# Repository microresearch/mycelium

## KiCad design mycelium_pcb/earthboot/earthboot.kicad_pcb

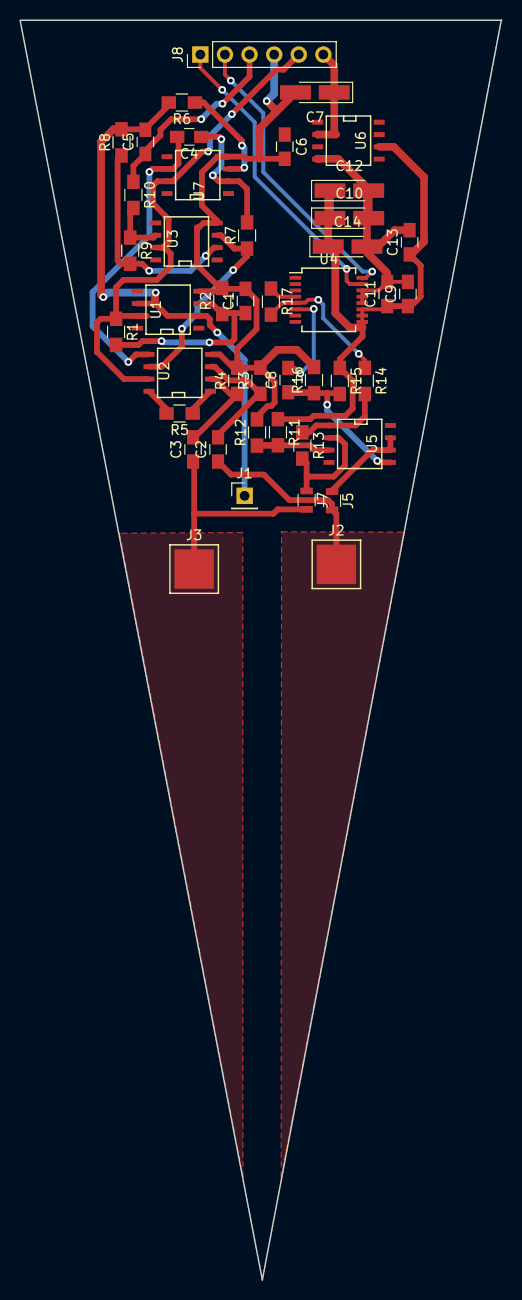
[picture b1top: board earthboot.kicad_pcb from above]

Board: 2 copper layers, 49.7 x 130.0 mm, 44 parts (0 on the bottom side), 29 nets.

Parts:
C1, C4: 100N; C_0805_HandSoldering
C2, C3: 10n; C_0805_HandSoldering
C5: 0.47uF; C_0805_HandSoldering
C6, C9, C11, C13: 100n; C_0805_HandSoldering
C7, C10, C12, C14: 1uF; CP_Tantalum_Case-A_EIA-3216-18_Hand
C8: 47n; C_0805_HandSoldering
J1: Conn_01x01; Socket_Strip_Straight_1x01_Pitch2.54mm
J2, J3: Conn_01x01; 1Pin
J5, J7: GS2; R_0805
J8: Conn_01x06; Socket_Strip_Straight_1x06_Pitch2.54mm
R1, R2, R10: 10K; R_0805_HandSoldering
R3, R4: 10M; R_0805_HandSoldering
R5, R8: 1K; R_0805_HandSoldering
R6, R7: 200K; R_0805_HandSoldering
R9: 390K; R_0805_HandSoldering
R11, R12, R15, R16: 47K; R_0805_HandSoldering
R13, R17: RFB; R_0805_HandSoldering
R14: 22K; R_0805_HandSoldering
U1, U3, U7: OP27; SOIC-8-N
U2: AD620; SOIC-8-N
U4: AD5933; SSOP-16_5.3x6.2mm_Pitch0.65mm
U5: AD8606; SOIC-8-N
U6: ADR423; SOIC-8-N

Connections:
+5V: C6.1, C7.1, J8.6, U6.2
/620_OUT: C5.1, J8.3, R10.1
/5933_IN: J7.1, R13.2, U5.2
/5933_OUT: J5.1, U5.6, U5.7
/AGND: C5.2, J1.1, R6.2, R8.2, U1.2, U1.6
/SCL: J8.2, U4.16
/SDA: J8.1, U4.15
GND: C1.2, C6.2, C7.2, C9.2, C10.2, C11.2, C12.2, C13.2, C14.2, J8.4, R2.2, R3.2, R4.2, R12.2, R16.2, U1.4, U2.4, U3.4, U4.12, U4.13, U4.14, U6.4, U7.4
unnamed: C1.1, R1.2, R2.1, U1.3
unnamed: C3.2, R4.1, U2.2
unnamed: C2.2, R3.1, U2.3
unnamed: C4.1, R7.2, U7.2
unnamed: C4.2, U2.5, U7.6
unnamed: C8.1, R15.2, R16.1, U5.5
unnamed: C8.2, U4.6
unnamed: C2.1, J2.1, J5.2
unnamed: C3.1, J3.1, J7.2
unnamed: R5.1, U2.1
unnamed: R5.2, U2.8
unnamed: R6.1, U7.3
unnamed: R7.1, U2.6, U3.3
unnamed: R8.1, R9.2, U3.2
unnamed: R9.1, R10.2, U3.6
unnamed: R11.2, R12.1, U5.3
unnamed: R13.1, R14.2, U5.1
unnamed: R14.1, R17.2, U4.5
unnamed: R17.1, U4.4
VDD: C9.1, C10.1, C11.1, C12.1, C13.1, C14.1, R11.1, R15.1, U4.9, U4.10, U4.11, U6.6
VDDA: J8.5, R1.1, U1.7, U2.7, U3.7, U7.7

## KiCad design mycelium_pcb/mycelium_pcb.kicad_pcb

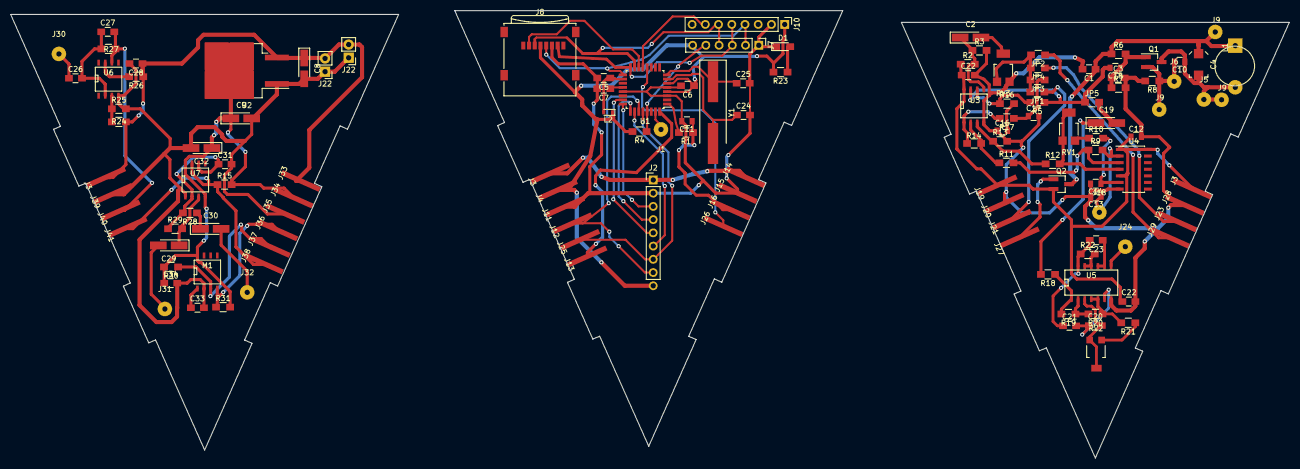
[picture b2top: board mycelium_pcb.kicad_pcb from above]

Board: 2 copper layers, 245.6 x 85.9 mm, 132 parts (0 on the bottom side), 75 nets.

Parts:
C1, C27: 10nF; C_0805_HandSoldering
C2: 1uF; CP_Tantalum_Case-A_EIA-3216-18_Hand
C3: 1nF; C_0805_HandSoldering
C4: 10pF-50pF; C_Trimmer_Murata_TZC3
C5, C6, C7, C22, C22#2, C26, C28, C31, C33: 100nF; C_0805_HandSoldering
C8, C9, C19: 10uF; CP_Tantalum_Case-A_EIA-3216-18_Hand
C10: 10pf or replace conns; C_0805
C11, C12: 100nF; C_0805
C13, C14: 100pF; C_0805
C16: 10nF; C_0805
C17: 1nF; C_0805
C18: 330nF; C_0805
C20, C21: 33pF; C_0805_HandSoldering
C23: 10pF; C_0805_HandSoldering
C24, C25: 22pF; C_0805_HandSoldering
C29, C30, C32: 2.2uF; CP_Tantalum_Case-A_EIA-3216-18_Hand
C34: 220nF; C_0805_HandSoldering
D1: LED_Small; LED_0805_HandSoldering
J1: BREAKOUT; SolderWirePad_single_1mmDrill
J2, J10: Conn_01x08; Socket_Strip_Straight_1x08_Pitch2.54mm
J3, J3#2, J3#3, J4, J11, J12, J13, J14, J15, J16, J25, J26, J33, J34, J35, J36, J37, J38: BREAKOUT; SolderWirePad_single_SMD_5x10mm
J5, J6: CAP; SolderWirePad_single_1mmDrill
J7: CONN_01X06; Socket_Strip_Straight_1x06_Pitch2.54mm
J8: Micro_SD_Card; microSD_Card_Receptacle_Wurth_693072010801
J9, J9#2: C; SolderWirePad_single_1mmDrill
J9#3, J24: ANTENNA; SolderWirePad_single_1mmDrill
J18: CONN_01X01; SolderWirePad_single_1mmDrill
J19, J20, J21, J23, J27, J28, J29, J39, J40, J41: EDGE; SolderWirePad_single_SMD_5x10mm
J22, J22#2: Conn_01x02; Socket_Strip_Straight_1x02_Pitch2.54mm
J30: RFIN; SolderWirePad_single_1mmDrill
J31, J32: MUSH; SolderWirePad_single_1mmDrill
JP1, JP2, JP3, JP4: J; R_0805_HandSoldering
JP5: Jumper_NO_Small; R_0805_HandSoldering
L1: COIL; INDUCTOR_V
L2: blocking; D_0603
M1: HIH6131; SOIC-8-N
Q1: BC547; SOT-23_Handsoldering
Q2: Q_PMOS_GSD; SOT-23_Handsoldering
R1: 68R; R_0805_HandSoldering
R2, R3, R27: 100K; R_0805_HandSoldering
R4, R5, R7, R10, R11, R12, R13, R14, R15, R24, R25, R30, R31: 10K; R_0805_HandSoldering
R6: 27K; R_0805_HandSoldering
R8: 470R; R_0805_HandSoldering
R9: 15K; R_0805_HandSoldering
R16: 1k5; R_0805_HandSoldering
R17: 6.8K; R_0805_HandSoldering
R18, R20: 4.7K; R_0805_HandSoldering
R19: 47K; R_0805_HandSoldering
R21, R22: 1K; R_0805_HandSoldering
R23: 330R; R_0805_HandSoldering
R26: 100R; R_0805_HandSoldering
R28: 390R; R_0805_HandSoldering
R29: 150K; R_0805_HandSoldering
RV1: 10K; Potentiometer_Trimmer-23Breichelt_larger
RV2: 2.5K; Potentiometer_Trimmer-23Breichelt
RV3: 10K; Potentiometer_Trimmer-23Breichelt
U1: ATMEGA168A-AU; TQFP-32_7x7mm_Pitch0.8mm
U2: LM1117-3.3; TO-263-2
U3: MCP602; SOIC-8-N
U4: HEF4093B; SOIC-14_3.9x8.7mm_Pitch1.27mm
U5: 74HC04; SOIC-14_N
U6: OP07; SOIC-8-N
U7: LMC555xM; SOIC-8-N
Y1: 16 MHz; Crystal_SMD_HC49-SD_HandSoldering

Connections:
+3V3: C6.1, C9.1, C32.1, C34.1, J2.8, J4.1, J7.6, J8.4, J10.1, J34.1, L2.1, M1.8, R4.2, R15.2, R23.2, R30.2, R31.2, U1.4, U1.6, U2.2, U7.4, U7.8
+5V: J2.1, J3#3.1, J14.1
/ADC_CO2: J2.6, U1.26
/ADC_LIGHT: J2.5, U1.23
/ADC_MUSHROOM: J2.3, U1.24
/MISO: J7.3, J8.7, J10.5, U1.16
/MOSI: J7.4, J8.3, J10.6, U1.15
/MUSH_555: J13.1, U1.32
/PWM_LP_OUT: C11.1, J16.1, R1.1
/PWM_OUT: R1.2, U1.1
/RF_EN: J26.1, U1.12
/SCK: J7.2, J8.5, J10.4, U1.17
/SCL: J2.7, J25.1, U1.28
/SDA: J2.8, J12.1, U1.27
/SPARE_ADC: J2.4, U1.25
/SS: J8.2, U1.14
/TEMP_CS: J10.7, U1.13
/TX: J1.1, U1.31
/fm radio/555_OUTT: J29.1, JP2.1
/fm radio/HF_OUTT: J23.1, JP4.1
/fm radio/PWM_LF_OUTT: J21.1, JP1.1
/fm radio/RF_EN: J27.1, Q2.1
/fm radio/THER_OUT: C17.1, JP3.1, R17.1
/sensorboard/HF_OUTT: C27.2, J40.1, R27.1, U6.6
/sensorboard/MUSH_555: J38.1, J41.1, R15.1, U7.7
/sensorboard/SCL: J37.1, M1.3, R30.1
/sensorboard/SDA: J36.1, M1.4, R31.1
GND: C1.2, C3.2, C5.2, C6.2, C7.2, C8.2, C9.2, C11.2, C12.2, C13.2, C14.2, C16.1, C17.2, C22.2, C22#2.2, C24.2, C25.2, C28.2, C31.2, C32.2, C33.2, C34.2, D1.1, J2.2, J7.1, J8.6, J10.2, J11.1, J15.1, J20.1, J22.1, J22#2.1, J28.1, J35.1, J39.1, M1.2, R3.2, R7.2, R8.2, R13.2, R25.2, RV3.3, U1.3, U1.5, U1.21, U2.1, U3.4, U4.7, U5.7, U6.4, U7.1
unnamed: C1.1, C4.1, J9#2.1, L1.1, Q2.3, R6.1
unnamed: C2.1, R2.2, R3.1, U3.5
unnamed: C2.2, RV3.2
unnamed: C5.1, L2.2, U1.18
unnamed: C7.1, U1.20
unnamed: C4.2, C10.1, J5.1, J9.1, L1.2, Q1.3
unnamed: C10.2, J6.1, J9#3.1, Q1.2, R8.1
unnamed: C13.1, J18.1, R9.2, U4.2
unnamed: C14.1, R10.2, U4.6
unnamed: C16.2, R16.2
unnamed: C3.1, C18.1, Q1.1, R6.2, R7.1
unnamed: C18.2, JP5.1, R5.1, U3.7
unnamed: C19.1, R18.2
unnamed: C19.2, JP5.2
unnamed: C20.1, C21.2, U5.6
unnamed: C20.2, RV2.2, RV2.3, U5.3
unnamed: C21.1, C23.2, R22.1, U5.13
unnamed: C23.1, U5.9, U5.10
unnamed: C24.1, U1.7, Y1.2
unnamed: C25.1, U1.8, Y1.1
unnamed: C26.1, J30.1
unnamed: C26.2, C27.1, R27.2, U6.2
unnamed: C29.1, R29.2, U7.3
unnamed: C29.2, J31.1
unnamed: C30.1, R28.1
unnamed: C30.2, J32.1
unnamed: C31.1, R28.2, R29.1, U7.2, U7.6
unnamed: C33.1, M1.1
unnamed: D1.2, R23.1
unnamed: J7.5, R4.1, U1.29
unnamed: J24.1, U5.8
unnamed: JP1.2, JP2.2, JP3.2, JP4.2, RV3.1
unnamed: R10.1, RV1.3
unnamed: R11.1, R14.2, U3.2
unnamed: R9.1, R11.2, U4.3
unnamed: R12.1, R13.1, U3.3
unnamed: R12.2, RV1.1, RV1.2, U4.4
unnamed: R14.1, R17.2, U3.1
unnamed: R5.2, R16.1, U3.6
unnamed: R18.1, R19.2, U5.1
unnamed: R19.1, R20.2, U5.2
unnamed: R20.1, R21.2, U5.4, U5.5
unnamed: R21.1, RV2.1
unnamed: R22.2, U5.11, U5.12
unnamed: R24.2, R25.1, U6.3
unnamed: R26.2, U6.7
VCC: C8.1, C12.1, C22.1, C22#2.1, C28.1, J3.1, J3#2.1, J19.1, J22.2, J22#2.2, J33.1, Q2.2, R2.1, R24.1, R26.1, U2.3, U3.8, U4.1, U4.5, U4.14, U5.14

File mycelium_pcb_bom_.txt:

Component	Description	Part	References	Value	Footprint	Quantity Per PCB	Datasheet	Notes

1	Unpolarized capacitor	C	C11 C12	100nF	C_0805	2 H		
2	Unpolarized capacitor	C	C5 C6 C7 C22 C26 C28 C31 C33	100nF	C_0805_HandSoldering	8 H

3	Unpolarized capacitor	C	C13 C14	100pF	C_0805	2 X		

4	Unpolarized capacitor	C	C1 C27	10nF	C_0805_HandSoldering	2 H		

5	Unpolarized capacitor	C	C23	10pF	C_0805_HandSoldering	1 H		

6	Trimmable capacitor	CTRIM	C4	10pF-50pF	C_Trimmer_Murata_TZC3	1		TZC03 30P (reich)X
7	Unpolarized capacitor	C	C10	10pf or replace conns	C_0805	1 H		

8	Polarised capacitor	CP	C8 C9 C19	10uF	CP_Tantalum_Case-A_EIA-3216-18_Hand	3 H		

9	Unpolarized capacitor	C	C17	1nF	C_0805	1		H
10	Unpolarized capacitor	C	C3	1nF	C_0805_HandSoldering	1 H		
11	Polarised capacitor	CP	C2	1uF	CP_Tantalum_Case-A_EIA-3216-18_Hand	1 H

12	Unpolarized capacitor	C	C29 C30	2.2uF	CP_Tantalum_Case-A_EIA-3216-18_Hand	2 (mouser)		
13	Polarised capacitor	CP	C32	2.2uF	CP_Tantalum_Case-A_EIA-3216-18_Hand	1 		

14	Polarised capacitor	CP	C34	220nF	C_0805_HandSoldering	1 X		

15	Unpolarized capacitor	C_Small	C24 C25	22pF	C_0805_HandSoldering	2 H		

16	Unpolarized capacitor	C	C18	330nF	C_0805	1 X		
17	Unpolarized capacitor	C	C20 C21	33pF	C_0805_HandSoldering	2		
18	Unpolarized capacitor	C	C16	4.7nF	C_0805	1 X		



19	LED, small symbol	LED_Small	D1	LED_Small	LED_0805_HandSoldering	1 - HAVE		


20		CONN_01X01	J9 J24	ANTENNA	SolderWirePad_single_1mmDrill	2		
21		CONN_01X01	J1 J3 J4	BREAKOUT	SolderWirePad_single_1mmDrill	3		
22		CONN_01X01	J11 J12 J13 J14 J15 J16 J25 J26 J33 J34 J35 J36 J37 J38	BREAKOUT	SolderWirePad_single_SMD_5x10mm	14		
23		CONN_01X01	J5 J6	CAP	SolderWirePad_single_1mmDrill	2		
24		CONN_01X01	J17 J18	CONN_01X01	SolderWirePad_single_1mmDrill	2		
25		CONN_01X06	J7	CONN_01X06	Socket_Strip_Straight_1x06_Pitch2.54mm	1		
26	Generic connector, single row, 01x02	Conn_01x02	J22	Conn_01x02	Socket_Strip_Straight_1x02_Pitch2.54mm	1		
27	Generic connector, single row, 01x08	Conn_01x08	J2 J10	Conn_01x08	Socket_Strip_Straight_1x08_Pitch2.54mm	2		
28		CONN_01X01	J19 J20 J21 J23 J27 J28 J29 J39 J40 J41	EDGE	SolderWirePad_single_SMD_5x10mm	10		
29		CONN_01X01	J31 J32	MUSH	SolderWirePad_single_1mmDrill	2



30	Micro SD Card Socket	Micro_SD_Card	J8	Micro_SD_Card	microSD_Card_Receptacle_Wurth_693072010801	1	http://katalog.we-online.de/em/datasheet/693072010801.pdf	710-693072010801 (mouser) X

31		CONN_01X01	J30	RFIN	SolderWirePad_single_1mmDrill	1		
32	Jumper, normally open	Jumper_NO_Small	JP1 JP2 JP3 JP4 JP5	Jumper_NO_Small	R_0805_HandSoldering	5		
33	Inductor	L	L1	COIL	INDUCTOR_V	1		0.8mmm handwound coil

34	Inductor	L	L2	blocking	D_0603	1		81-BLM18BD252SN1D - have WORM
35		HIH6131	M1	HIH6131	SOIC-8-N	1		HIH6131-021-001 (mouser) X

36		BC547	Q1	2n2222	SOT-23_Handsoldering	1		2N 2222A SMD (reich) - X

37	Transistor P-MOSFET with substrate diode (general)	Q_PMOS_GSD	Q2	Q_PMOS_GSD	SOT-23_Handsoldering	1		NXP2301P-reichelt -X

38	Resistor	R	R2 R3 R27	100K	R_0805_HandSoldering	3 H		
39	Resistor	R	R26	100R	R_0805_HandSoldering	1 H		
40	Resistor	R	R4 R5 R7 R10 R11 R12 R13 R14 R15 R24 R25 R30 R31	10K	R_0805_HandSoldering	13 H		
41	Resistor	R	R29	150K	R_0805_HandSoldering	1 H		
42	Resistor	R	R9	15K	R_0805_HandSoldering	1 H		
43	Resistor	R	R21 R22	1K	R_0805_HandSoldering	2 H		
44	Resistor	R	R16	1K5	R_0805_HandSoldering	1 H		
45	Resistor	R	R6	27K	R_0805_HandSoldering	1 H-WORM		
46	Resistor	R	R23	330R	R_0805_HandSoldering	1 H		
47	Resistor	R	R28	390R	R_0805_HandSoldering	1 X		
48	Resistor	R	R18 R20	4.7K	R_0805_HandSoldering	2 H		
49	Resistor	R	R8	470R	R_0805_HandSoldering	1 H		
50	Resistor	R	R19	47K	R_0805_HandSoldering	1 H		
51	Resistor	R	R17	6.8K	R_0805_HandSoldering	1 X		
52	Resistor	R	R1	68R	R_0805_HandSoldering	1 X		

53	Trim-Potentiometer	POT_TRIM	RV1 RV3	10K	Potentiometer_Trimmer-EVM3E	2		23B-2.0K (reich)X
54	Trim-Potentiometer	POT_TRIM	RV2	2.5K	Potentiometer_Trimmer-EVM3E	1		23B-10.0k (reich) X

55	hex inverter	74HC04	U5	74HC04	SOIC-14_N	1	http://www.nxp.com/documents/data_sheet/74HC_HCT04.pdf	X

56	TQFP32, 16k Flash, 1kB SRAM, 512B EEPROM	ATMEGA168A-AU	U1	ATMEGA168A-AU	TQFP-32_7x7mm_Pitch0.8mm	1	http://www.atmel.com/images/atmel-8271-8-bit-avr-microcontro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 - HAVE	

57	Quad 2-Input NAND Schmitt Trigger, SOIC-14	HEF4093B	U4	HEF4093B	SSOP-14	1	https://assets.nexperia.com/documents/data-sheet/HEF4093B.pdfX

58	800mA Low-Dropout Linear Regulator, 1.8V fixed output, TO-220/TO-252/TO-263/SOT-223	LM1117-3.3	U2	LM1117-3.3	TO-263-2	1	http://www.ti.com/lit/ds/symlink/lm1117.pdf - HAVE

59	Timer, DIP-8/SOIC-8/SSOP-8	LMC555xM	U7	LMC555xM	SOIC-8-N	1	http://www.ti.com/lit/ds/symlink/lm555.pdf X	

60	Dual Operational Amplifiers, DIP-8/SOIC-8/TSSOP-8/VSSOP-8	MCP602	U3	MCP602	SOIC-8-N	1	http://www.ti.com/lit/ds/symlink/lm358.pdf X

61	Single Ultra-Low Offset Voltage Operational Amplifier, DIP-8/SOIC-8	OP07	U6	OP07	SOIC-8-N	1	http://www.analog.com/media/en/technical-documentation/data-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 X	

62	Two pin crystal, small symbol	Crystal_Small	Y1	16 MHz	Crystal_SMD_HC49-SD_HandSoldering	1 X		





Component Groups:	62
Component Count:	127
Fitted Components:	127
Number of PCBs:	1
Total components:	127
Schematic Version:	
Schematic Date:	
BoM Date:	Mon 06 Aug 2018 17:54:32 CEST
Schematic Source:	/root/projects/myc/mycelium_pcb/mycelium_pcb.sch
KiCad Version:	Eeschema (6.0.0-rc1-dev-233-g53236a383)

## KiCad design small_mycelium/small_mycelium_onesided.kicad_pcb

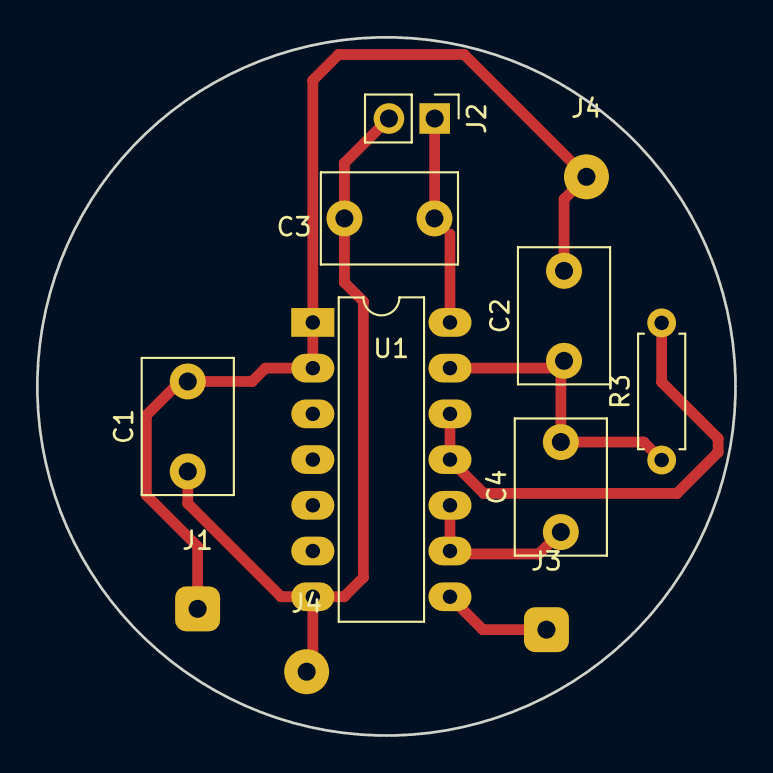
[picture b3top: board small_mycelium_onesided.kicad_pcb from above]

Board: 2 copper layers, 38.8 x 38.8 mm, 11 parts (0 on the bottom side), 9 nets.

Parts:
C1, C4: 10pF; C_Disc_D7.5mm_W5.0mm_P5.00mm
C2: 33pF; C_Disc_D7.5mm_W5.0mm_P5.00mm
C3: 100nF; C_Disc_D7.5mm_W5.0mm_P5.00mm
J1, J3, J4, J4#2: SolderWirePad_single_1mmDrill
J2: Pin_Header_Straight_1x02_Pitch2.54mm
R3: 1K; R_Axial_DIN0207_L6.3mm_D2.5mm_P7.62mm_Horizontal
U1: 74HC04; DIP-14_W7.62mm_LongPads

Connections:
GND: C1.1, C3.2, J2.2, J4.1, U1.7
unnamed: U1.3, U1.4
unnamed: C2.1, C4.2, R3.1, U1.13
unnamed: C1.2, C2.2, J1.1, J4#2.1, U1.1, U1.2
unnamed: C4.1, U1.9, U1.10
unnamed: J3.1, U1.8
unnamed: U1.5, U1.6
unnamed: R3.2, U1.11, U1.12
VCC: C3.1, J2.1, U1.14

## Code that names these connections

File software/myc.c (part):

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void init_all() {

  // pins: OC2B is PWM OUT (PD3), INT0 (PD2) is 555 counter IN
// PC0,1,2,3: ADC0+ = adc_light, adc_mushroom, spare_adc, adc_co2
// PB0 is RF ENABLE=OUT 

// PB1 is temp_cs and rest of temp as usual setup MAX31865 (port library)
  
  DDRD=0x08;  // PD3
  DDRB|=0x01; // PB0 and for SD card  
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
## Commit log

2018-06-28 first myc
2018-07-03 break down schematics
2018-07-04 to check all
2018-07-10 footprints
2018-07-16 placings
2018-07-16 trax
2018-07-18 adding earthboot device
2018-07-19 ready to split
2018-07-19 soldermasking
2018-07-19 splits
2018-07-20 dixed 5933 size
2018-07-21 fet/radio
2018-07-23 zoning
2018-07-23 gerbers etc...
2018-08-13 update all else...
2018-08-13 for layouts
2018-08-13 pdfs
2018-08-14 soft
2018-08-15 fixes to earth
2018-08-20 added HIH6131 - tested and working
2018-08-20 will do raw writes/reads to sd
2018-08-21 MAX31865 reading SPI addded
2018-08-22 added RDA5807
2018-08-23 parts
2018-08-27 types
2018-08-27 added microbd, noise
2018-08-27 lib quest
2018-08-30 added audio test bed
2018-09-03 wormed
2018-09-04 afsk
2018-09-05 latestxx
2018-10-17 ard/platform tests
2018-10-18 extra modulations
2018-10-21 mini mycelium for workshop
2018-10-22 small mycelium transmission circuit for workshop
2018-10-23 for_dan
2018-10-25 finals

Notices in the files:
software/myc.c:
license:GPL-2.0+
